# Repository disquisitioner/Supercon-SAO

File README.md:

# Supercon SAO Projects

Each year the Hackaday Supercon conference designs a unique badge that attendees can wear but also program.  While every year's badge is very different, they all incorporate an
add-on interface (called the ["Supercon Add-On"](https://hackaday.io/project/175182-simple-add-ons-sao) or "SAO") that exposes power and digital communications in a standardized configuration.

I'm attending Supercon for the first time in 2024 and am keen to try my hand at badge programming and SAO development. This repo serves as a collection point for software and hardware designs in support of my SAO voyage of discovery.  Everything is organized by year, as the badge, badge programming environment, and documentation changes every year.

Part of the challenge in developing an SAO add-on is that details of the badge are not released until about four weeks before the conference.  It pays, therefore, to be as prepared as possible but also stay flexible so you can react and probably re-design once actual badge specifications are known.

My newbie attempt for 2024 is to build an add-on that monitors air quality around the  badge wearer and uses a simple "stoplight" with red, yellow and green LEDs to translate current CO2 levels into subjective "good" (green), "warning" (yellow) and "alert!" (red) values.  We'll see how that goes...

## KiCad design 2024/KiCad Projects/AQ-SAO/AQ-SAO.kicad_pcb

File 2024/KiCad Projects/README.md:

# Printed Circuit Board Designs

Part of the fun and challenge of building a Supercon badge add-on is designing a printed circuit board (PCB) to use in assembling the add-on.  I've only ever designed and built one  PCB and that was a decade ago as part of taking a class on PCB design.

Happily tools for PCB design have gotten better and freely available as open source.  Among the SAO add-on community there was lots of love for [KiCad](https://www.kicad.org/), so I gave it a try.  The getitng started documentation is very helpful, taking you through the process of designing a schematic for the PCB, laying out the board itself, using tools to check the designs, and previewing everything before submitting it for manufacture. 

Even so, PCB design is a iterative process with lots of learn by doing, which means sending designs out for fabrication and discovering what you didn't quite get right when the boards come back.  Happily getting boards produced is quick and not particularly expensive!

The KiCad files are available here. 

## Schematic

Using the two GPIO digital lines in the SAO add-on interface to control the three LEDs in the "stoplight" requires some simple digital logic to translate the four possible values of those two lines taken together (00, 01, 10, and 11) into separate single lines that drive the LEDs. That's easily done through a combination of Boolean "and" and "not" gates, but for a variety of reasons it's more commonly the case that "nand" gates (for "not-and") are used.  It would take three "and" and three "not" gates (inverters) to do the logic translation, but if done with "nand" gates you need eight overall.  Happily the 7400 digital logic IC incorporates four nand gates into a single 14-pin package, so two of those ICs get the job done.

If you're not familar with digital logic see if you can determine from the schematic how the "nand" gates make it work.

## PCB Layout
The PCB is laid out with an eye towards how the finished add-on should look.  The three LEDs should be at the top of the add-on so they're easy to see.  They each need to be connected to the output of the digital logic circuit (nand gates) that drives them in translating the values of the two GPIO inputs from the SAO add-on connector, though each LED needs a resistor to set the proper drive current for consistent overall brightness.  There are connection points that allow the CO2 sensor to be connected to the four I2C lines from the SAO add-on connector, and four mounting holes spaced to line up with the mounting holes in the Adafruit SCD40 sensor add-on board so it can be secured atop the add-on board itself.

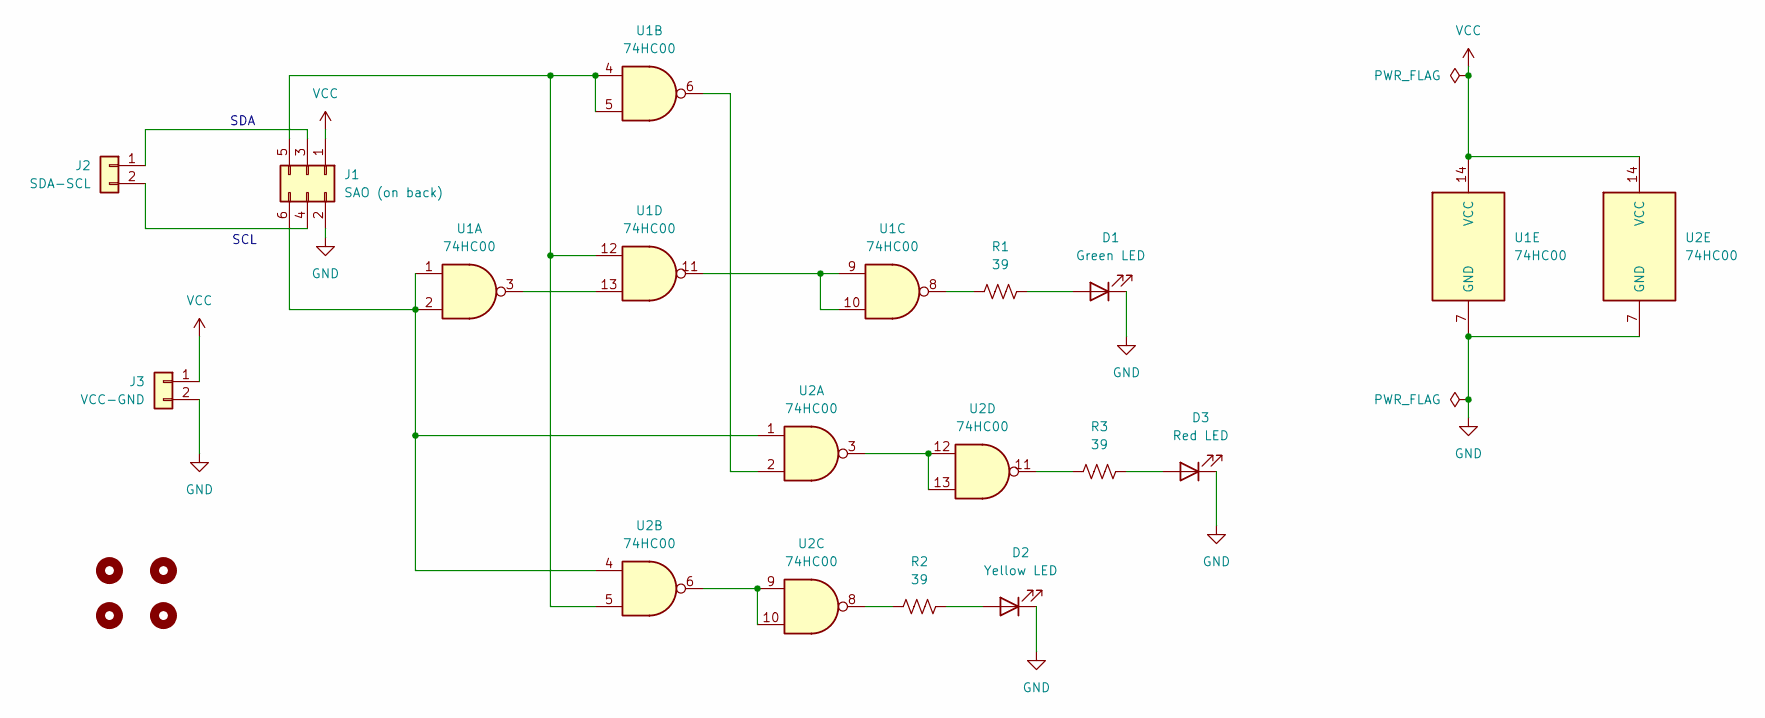
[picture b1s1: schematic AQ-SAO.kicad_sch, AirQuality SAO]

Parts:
D1: Green LED; LED_Rectangular_W5.0mm_H2.0mm
D2: Yellow LED; LED_Rectangular_W5.0mm_H2.0mm
D3: Red LED; LED_Rectangular_W5.0mm_H2.0mm
H1, H2, H3, H4: MountingHole; MountingHole_2.2mm_M2
J1: SAO (on back); PinHeader_2x03_P2.54mm_Vertical
J2: SDA-SCL; PinHeader_1x02_P2.54mm_Vertical
J3: VCC-GND; PinHeader_1x02_P2.54mm_Vertical
R1, R2, R3: 39; R_Axial_DIN0204_L3.6mm_D1.6mm_P5.08mm_Horizontal
U1, U2: 74HC00; DIP-14_W7.62mm

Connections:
GND: D1.1 (K), D2.1 (K), D3.1 (K), J1.2, J3.2, U1.7 (GND), U2.7 (GND)
unnamed: D1.2 (A), R1.2
unnamed: D2.2 (A), R2.2
unnamed: D3.2 (A), R3.2
unnamed: J1.3, J2.1
unnamed: J1.4, J2.2
unnamed: J1.5, U1.4, U1.5, U1.12, U2.5
unnamed: J1.6, U1.1, U1.2, U2.1, U2.4
unnamed: R1.1, U1.8
unnamed: R2.1, U2.8
unnamed: R3.1, U2.11
unnamed: U1.6, U2.2
unnamed: U1.9, U1.10, U1.11
unnamed: U1.3, U1.13
unnamed: U2.6, U2.9, U2.10
unnamed: U2.3, U2.12, U2.13
VCC: J1.1, J3.1, U1.14 (VCC), U2.14 (VCC)

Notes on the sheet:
SDA
SCL

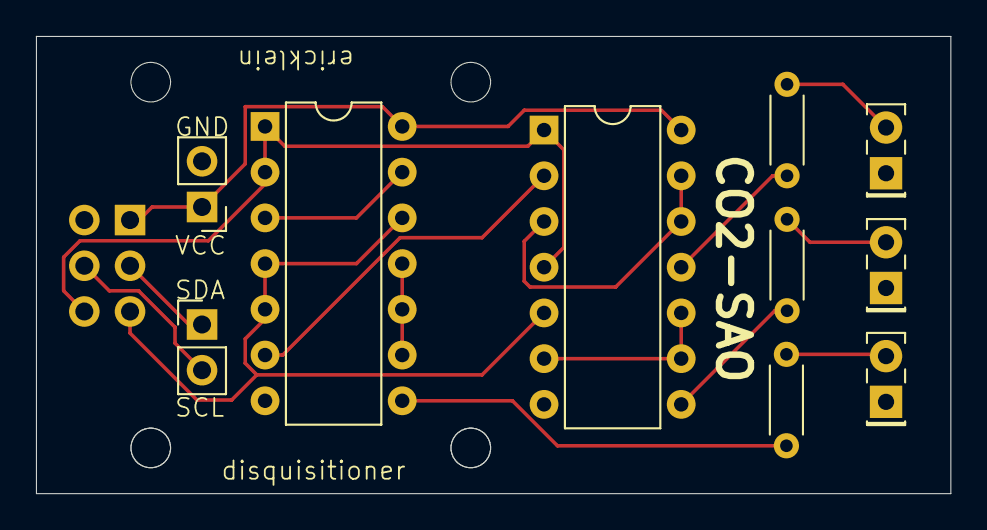
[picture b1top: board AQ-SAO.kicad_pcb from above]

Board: 2 copper layers, 50.8 x 25.4 mm, 15 parts (1 on the bottom side), 17 nets.

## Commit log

2024-09-29 2024: CircuitPython stoplight v0
2024-09-29 Initial overall README
2024-10-10 KiCad projects for CO2 add-on and SAO breakout
2024-10-10 Added 2024 README
2024-10-13 First MicroPython version
2024-10-13 Added README
2024-10-27 Update based on official badge announcement
2024-11-01 Adapting code to run on the actual 2024 badge
2024-11-01 JSON config file support
2024-11-02 Separated Pico W and Supercon Badge variants
2024-11-02 Clean up variant versions
2024-11-02 Updating README from Supercon day 1
2024-11-03 Updating to reflect onsite development at Supercon
2024-11-03 Updating README
2024-11-03 Updating KiCad PCB files and README
